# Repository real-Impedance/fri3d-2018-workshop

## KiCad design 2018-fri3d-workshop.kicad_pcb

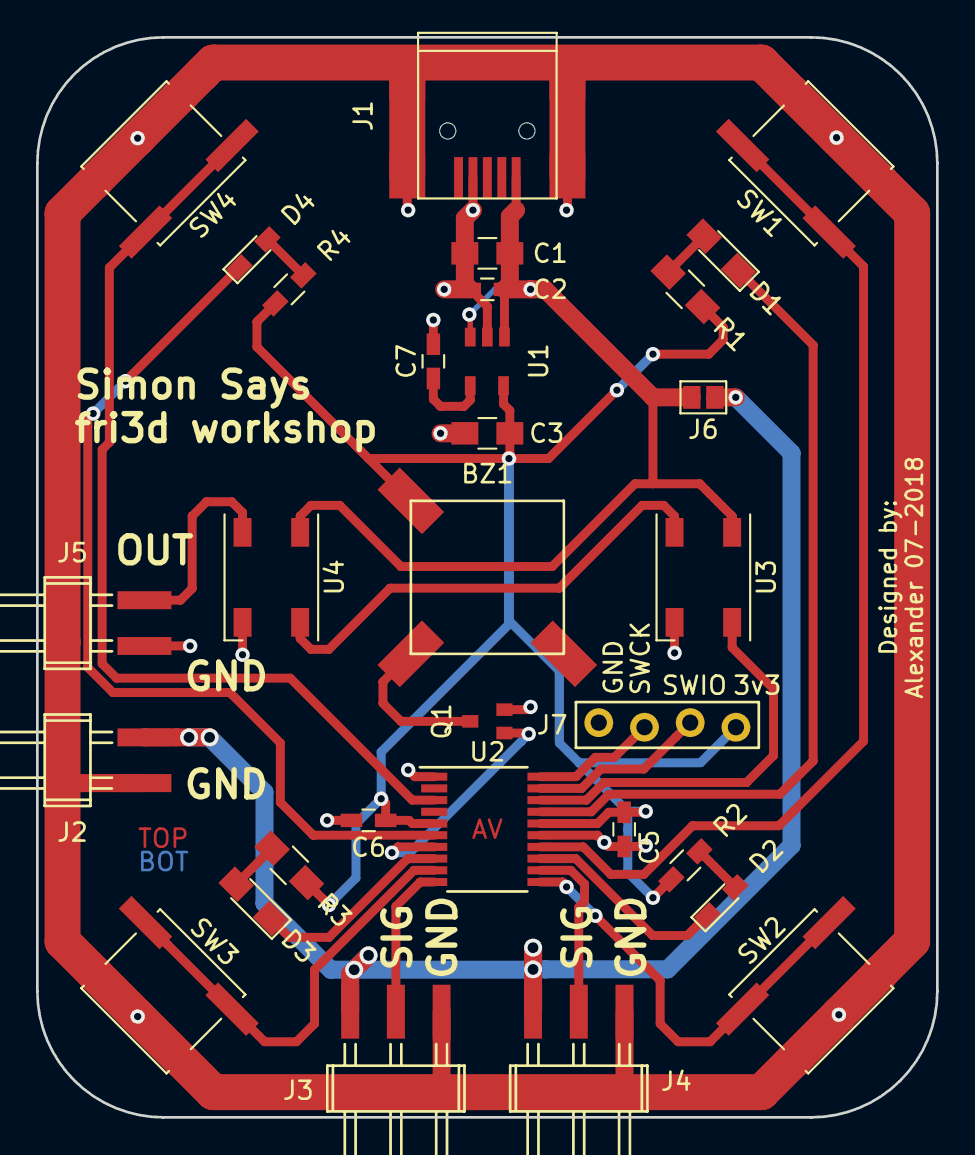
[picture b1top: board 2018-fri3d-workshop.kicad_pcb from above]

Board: 2 copper layers, 50.0 x 60.0 mm, 31 parts (0 on the bottom side), 26 nets.

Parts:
BZ1: Buzzer; SMD-buzzer-8.5x8.5
C1, C3: 1µF/X7R; C_0805_HandSoldering
C2, C5, C6: 100nF; C_0603_HandSoldering
C7: 22nF; C_0603_HandSoldering
D1, D3: LED; LED_0805_HandSoldering
D2, D4: LED; LED_0603_HandSoldering
J1: USB_B; USB_Mini-B_mod
J2, J5: Conn_01x02; Pin_Header_Angled_1x02_Pitch2.54mm
J3, J4: Conn_01x03_m; Pin_Header_Angled_1x03_Pitch2.54mm
J6: GS2
J7: Conn_01x04; Pin_Header_NoSolder_1x04_Pitch2.54mm
Q1: DMG1012UW; SOT-323
R1, R3: 220R; R_0805_HandSoldering
R2, R4: 220R; R_0603_HandSoldering
SW1, SW2, SW3, SW4: SW_SPST; SW_SPST_EVQQ2
U1: RT9193-33; SOT23-5
U2: STM32F030F4Px; TSSOP-20_4.4x6.5mm_Pitch0.65mm
U3, U4: WS2812B; LED_WS2812B-PLCC4

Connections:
3V3: BZ1.1, C3.1, C5.1, C6.1, J7.1, R1.1, R2.1, R3.1, R4.1, U1.5, U2.5, U2.16
/ButLD: SW3.1, U2.9
/ButLU: SW4.1, U2.3
/ButRD: SW2.1, U2.11
/ButRU: SW1.1, U2.14
/Buzzer: Q1.2, U2.7
/LedLD: D3.1, U2.8
/LedLU: D4.1, U2.6
/LedRD: D2.1, U2.13
/LedRU: D1.1, U2.17
/SWCLK: J7.3, U2.20
/SWDIO: J7.2, U2.19
/Servo1: J3.2, U2.10
/Servo2: J4.2, U2.12
/WS2812: U2.18, U3.4
GND: C1.2, C2.2, C3.2, C5.2, C6.2, C7.2, J1.4, J2.2, J3.3, J4.3, J5.2, J7.4, Q1.3, SW1.2, SW2.2, SW3.2, SW4.2, U1.2, U2.1, U2.15, U3.3, U4.3
unnamed: BZ1.2, Q1.1
unnamed: C7.1, U1.4
unnamed: D1.2, R1.2
unnamed: D2.2, R2.2
unnamed: D3.2, R3.2
unnamed: D4.2, R4.2
unnamed: J5.1, U4.2
unnamed: U3.2, U4.4
Vservo: J2.1, J3.1, J4.1, J6.1
Vusb: C1.1, C2.1, J1.1, J6.2, U1.1, U1.3, U3.1, U4.1

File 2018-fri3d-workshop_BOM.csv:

"Source:","/home/alexander/Documenten/KiCad/fri3d-2018-workshop/2018-fri3d-workshop.sch"
"Date:","zo 15 jul 2018 17:46:39 CEST"
"Tool:","Eeschema 4.0.7"
"Generator:","/lib/kicad/plugins/bom_csv_grouped_by_value_with_fp.py"
"Component Count:","31"
"Ref","Qnty","Value","Cmp name","Footprint","Description","Vendor"
"BZ1, ","1","Buzzer","Buzzer","My_Footprints:SMD-buzzer-8.5x8.5","Buzzer, polar",""
"C1, C3, ","2","1µF/X7R","C","Capacitors_SMD:C_0805_HandSoldering","Unpolarized capacitor",""
"C5, C6, C2, ","3","100nF","C","Capacitors_SMD:C_0603_HandSoldering","Unpolarized capacitor",""
"C7, ","1","22nF","C","Capacitors_SMD:C_0603_HandSoldering","Unpolarized capacitor",""
"D1, D3, ","2","LED","LED","LEDs:LED_0805_HandSoldering","LED generic",""
"D2, D4, ","2","LED","LED","LEDs:LED_0603_HandSoldering","LED generic",""
"J1, ","1","USB_B","USB_B","Connectors:USB_Mini-B","USB Type B connector",""
"J2, J5, ","2","Conn_01x02","Conn_01x02","My_Footprints:Pin_Header_Angled_1x02_Pitch2.54mm","Generic connector, single row, 01x02",""
"J3, J4, ","2","Conn_01x03_m","Conn_01x03_m","My_Footprints:Pin_Header_Angled_1x03_Pitch2.54mm","Generic connector, single row, 01x03",""
"J6, ","1","GS2","GS2","Connectors:GS2","2-pin jumper/solder bridge",""
"J7, ","1","Conn_01x04","Conn_01x04","My_Footprints:Pin_Header_NoSolder_1x04_Pitch2.54mm","Generic connector, single row, 01x04",""
"Q1, ","1","DMG1012UW","DMG1012UW","My_Footprints:SOT-323","Transistor N-MOSFET (general)",""
"R1, R3, ","2","220R","R","Resistors_SMD:R_0805_HandSoldering","Resistor",""
"R2, R4, ","2","220R","R","Resistors_SMD:R_0603_HandSoldering","Resistor",""
"SW1, SW2, SW3, SW4, ","4","SW_SPST","SW_SPST","Buttons_Switches_SMD:SW_SPST_EVQQ2","Single Pole Single Throw (SPST) switch",""
"U1, ","1","RT9193-33","RT9193-33","My_Footprints:SOT23-5","",""
"U2, ","1","STM32F030F4Px","STM32F030F4Px","Housings_SSOP:TSSOP-20_4.4x6.5mm_Pitch0.65mm","",""
"U4, U3, ","2","WS2812B","WS2812B","LEDs:LED_WS2812B-PLCC4","",""

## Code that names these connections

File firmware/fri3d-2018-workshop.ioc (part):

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Mcu.Name=STM32F030F4Px
Mcu.Package=TSSOP20
Mcu.UserName=STM32F030F4Px
PA0.GPIOParameters=GPIO_Label
PA0.GPIO_Label=LedLU
PA0.Signal=GPIO_Output
PA1.GPIOParameters=GPIO_Label
PA1.GPIO_Label=Buzzer
PA1.Signal=GPIO_Output
PA10.GPIOParameters=GPIO_Label
PA10.GPIO_Label=WS2812C
PA10.Signal=GPIO_Output
PA13.Mode=Serial_Wire
PA13.Signal=SYS_SWDIO
PA14.Mode=Serial_Wire
PA14.Signal=SYS_SWCLK
PA2.GPIOParameters=GPIO_Label
PA2.GPIO_Label=LedLD
PA2.Signal=GPIO_Output
PA3.GPIOParameters=GPIO_PuPd,GPIO_Label
PA3.GPIO_Label=ButLD
PA3.GPIO_PuPd=GPIO_PULLUP
PA3.Signal=GPIO_Input
PA4.GPIOParameters=GPIO_Label
PA4.GPIO_Label=Servo1
PA4.Signal=GPIO_Output
PA5.GPIOParameters=GPIO_PuPd,GPIO_Label
PA5.GPIO_Label=ButRD
PA5.GPIO_PuPd=GPIO_PULLUP
PA5.Signal=GPIO_Input
PA6.GPIOParameters=GPIO_Label
PA6.GPIO_Label=Servo2
PA6.Signal=GPIO_Output
PA7.GPIOParameters=GPIO_Label
PA7.GPIO_Label=LedRD
PA7.Signal=GPIO_Output
PA9.GPIOParameters=GPIO_Label
PA9.GPIO_Label=LedRU
PA9.Signal=GPIO_Output
PB1.GPIOParameters=GPIO_PuPd,GPIO_Label
PB1.GPIO_Label=ButRU
PB1.GPIO_PuPd=GPIO_PULLUP
PB1.Signal=GPIO_Input
PF1-OSC_OUT.GPIOParameters=GPIO_PuPd,GPIO_Label
PF1-OSC_OUT.GPIO_Label=ButLU
PF1-OSC_OUT.GPIO_PuPd=GPIO_PULLUP
PF1-OSC_OUT.Signal=GPIO_Input
board=custom

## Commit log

2018-07-15 Delete 2018-fri3d-workshop-201807151817.zip
    not needed in here
2018-07-15 added designer/descripion to silkscreen
2018-08-22 Fixed EN and GND pin regulator
2018-08-22 create firmware folder
2018-08-22 upload off first part off sw4stm32 project
2018-08-22 upload off second part off sw4stm32 project
2018-08-22 upload off third and last part off sw4stm32 project
    github refuses to upload the .cproject, .mxproject, .project and .settings files. I hope you don't need them. Or can tell me a solution.
2018-08-28 Create LICENSE
    added a license to this work.
2018-08-28 Update LICENSE
